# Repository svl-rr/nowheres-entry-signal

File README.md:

# SVL (Nowheres) Yard Entry Signal Driver

This is Arduino firmware for a microcontroller that has a pushbutton that
the yardmaster pushes to clear the signal. When the button is pressed,
the signal goes green for a constant amount of time and the buzzer plays
a chirping tone. After the time is up, the signal goes red again.

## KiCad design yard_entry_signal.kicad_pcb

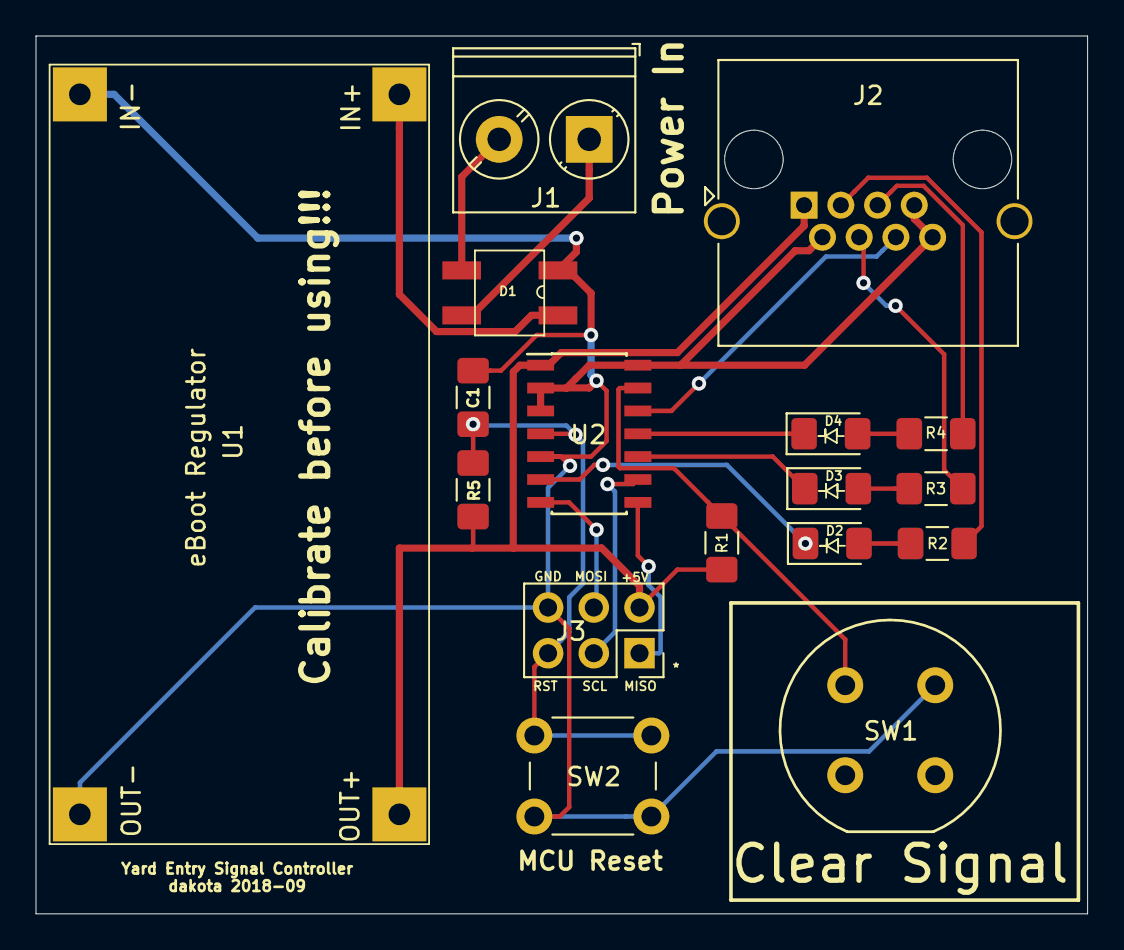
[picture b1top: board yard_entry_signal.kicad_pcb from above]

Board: 2 copper layers, 58.4 x 48.8 mm, 17 parts (0 on the bottom side), 20 nets.

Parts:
C1: 10uF; C_1206_3216Metric_Pad1.42x1.75mm_HandSolder
D1: Rect; MBS
D2: Red; LED_1206_HandSolder_Marked
D3: Yellow; LED_1206_HandSolder_Marked
D4: Green; LED_1206_HandSolder_Marked
J1: Conn_01x02; TerminalBlock_Phoenix_PT-1,5-2-5.0-H_1x02_P5.00mm_Horizontal
J2: RJ45; RJ45_Amphenol_RJHSE5380
J3: AVR-ISP-6; PinSocket_2x03_P2.54mm_Vertical
R1, R5: 10k; R_1206_3216Metric_Pad1.42x1.75mm_HandSolder
R2, R3, R4: 390; R_1206_3216Metric_Pad1.42x1.75mm_HandSolder
SW1: UsrBtn; Push_E-Switch_KS01Q01
SW2: Reset; SW_PUSH_6mm_H5mm
U1: eboot_regulator
U2: ATtiny44A-SSU; SOIC-14_3.9x8.7mm_P1.27mm

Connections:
+5V: J2.1, J3.2, R1.1, R5.2, U1.3, U2.1
/AC_PWR_1: D1.4, J1.2
/AC_PWR_2: D1.3, J1.1
/ATTiny44A/PA0: R1.2, SW1.1, U2.13
/ATTiny44A/PA2: D4.1, U2.11
/ATTiny44A/PA3: D3.1, U2.10
/ATTiny44A/PA7: D2.1, U2.6
/ATTiny44A/RESET_PB3: C1.1, J3.5, R5.1, SW2.1, U2.4
/ATTiny44A/SPI_MISO_PA5: J3.1, U2.8
/ATTiny44A/SPI_MOSI_PA6: J3.4, U2.7
/ATTiny44A/SPI_SCL_PA4: J3.3, U2.9
/Yard Signal Jack/Buzzer: J2.6, U2.12
/Yard Signal Jack/Green_Drain: J2.5, R4.2
/Yard Signal Jack/Red_Drain: J2.3, R2.2
/Yard Signal Jack/Yellow_Drain: J2.4, R3.2
GND: C1.2, D1.2, J2.2, J2.7, J2.8, J3.6, SW1.2, SW2.2, U1.2, U1.4, U2.2, U2.3, U2.5, U2.14
unnamed: D1.1, U1.1
unnamed: D2.2, R2.1
unnamed: D3.2, R3.1
unnamed: D4.2, R4.1

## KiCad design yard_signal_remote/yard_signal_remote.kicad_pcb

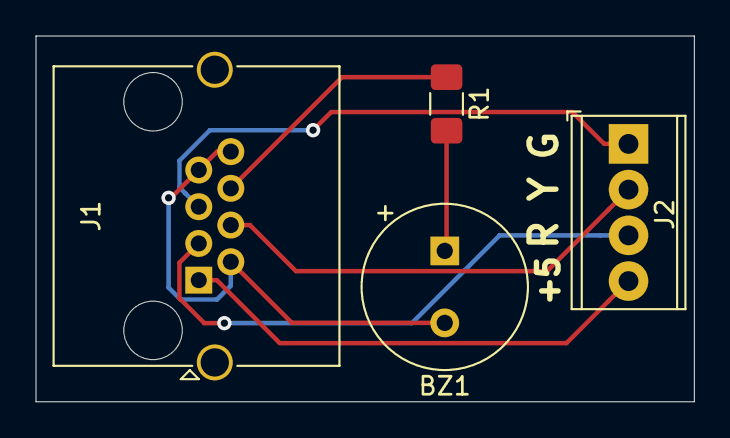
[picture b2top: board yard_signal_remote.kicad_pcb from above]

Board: 2 copper layers, 36.6 x 20.3 mm, 4 parts (0 on the bottom side), 7 nets.

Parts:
BZ1: Buzzer; MagneticBuzzer_CUI_CST-931RP-A
J1: RJ45; RJ45_Amphenol_RJHSE5380
J2: Conn_01x04_Female; TerminalBlock_Phoenix_MPT-0,5-4-2.54_1x04_P2.54mm_Horizontal
R1: 100; R_1206_3216Metric_Pad1.42x1.75mm_HandSolder

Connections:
+5V: J1.1, J2.4
/Buzzer: J1.6, R1.1
/Green_Drain: J1.5, J2.1
/Red_Drain: J1.3, J2.3
/Yellow_Drain: J1.4, J2.2
GND: BZ1.2, J1.2, J1.7, J1.8
unnamed: BZ1.1, R1.2

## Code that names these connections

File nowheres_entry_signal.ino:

#define SIGNAL_RED_PIN 7  // PA7, Tiny 6
#define SIGNAL_YELLOW_PIN 3  // PA3, Tiny 10
#define SIGNAL_GREEN_PIN 2  // PA2, Tiny 11
#define BUZZER_PIN 1  // Tiny 12
#define BUTTON_PIN 0 // PA0, Tiny 13
// #define LED_L_PIN 13

#define GREEN_TIME_MS 25000
#define YELLOW_TIME_MS 0  // disabled for now

#define BUZZER_NOTE_LENGTH_MS 20
#define BUZZER_REST_LENGTH_MS 50
#define BUZZER_TOTAL_SONG_LENGTH_MS 2000
#define BUZZER_PERIOD_MS (BUZZER_NOTE_LENGTH_MS + BUZZER_REST_LENGTH_MS)

unsigned long buttonPressedMs = 0;
unsigned short buzzerNoteAndRestStartTimeMs = 0;

void SetSignal(const int onPin) {
  digitalWrite(SIGNAL_RED_PIN, HIGH);
  digitalWrite(SIGNAL_YELLOW_PIN, HIGH);
  digitalWrite(SIGNAL_GREEN_PIN, HIGH);
  digitalWrite(onPin, LOW);
}

void PokeBuzzer(const unsigned long now_ms) {
  unsigned long msSinceButtonPress = now_ms - buttonPressedMs;
  if (buttonPressedMs > 0 && msSinceButtonPress < BUZZER_TOTAL_SONG_LENGTH_MS) {
    if (buzzerNoteAndRestStartTimeMs == 0) {
      buzzerNoteAndRestStartTimeMs = now_ms;
    }

    unsigned long currentNoteDurationMs = now_ms - buzzerNoteAndRestStartTimeMs;
    if (currentNoteDurationMs < BUZZER_NOTE_LENGTH_MS) {
      digitalWrite(BUZZER_PIN, HIGH);
    } else if (currentNoteDurationMs < BUZZER_PERIOD_MS) {
      digitalWrite(BUZZER_PIN, LOW);
    } else {
      // start a new note
      buzzerNoteAndRestStartTimeMs = 0;
    }
  } else {
    buzzerNoteAndRestStartTimeMs = 0;
    digitalWrite(BUZZER_PIN, LOW);
  }
}

void setup() {
  pinMode(SIGNAL_RED_PIN, OUTPUT);
  pinMode(SIGNAL_YELLOW_PIN, OUTPUT);
  pinMode(SIGNAL_GREEN_PIN, OUTPUT);
  pinMode(BUZZER_PIN, OUTPUT);
  pinMode(BUTTON_PIN, INPUT_PULLUP);
  // pinMode(LED_L_PIN, OUTPUT);

  SetSignal(SIGNAL_RED_PIN);
}

void loop() {
  unsigned long now_ms = millis();
  if (digitalRead(BUTTON_PIN) == LOW) { // active
    buttonPressedMs = now_ms;
    // digitalWrite(LED_L_PIN, HIGH);
    SetSignal(SIGNAL_GREEN_PIN);
  } else {
    // digitalWrite(LED_L_PIN, LOW);
  }

  PokeBuzzer(now_ms);

  unsigned long msSinceButtonPress = now_ms - buttonPressedMs;
  if (msSinceButtonPress > (GREEN_TIME_MS + YELLOW_TIME_MS)) {
    SetSignal(SIGNAL_RED_PIN);
  } else if (msSinceButtonPress > GREEN_TIME_MS) {
    SetSignal(SIGNAL_YELLOW_PIN);
  }
}

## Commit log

2018-06-24 Initial commit for rev 0 of nowheres yard entry signal driver
2018-06-24 Add readme
2018-11-30 Change pins to match ATTiny44A.
2018-11-30 Add PCBs for yard signal project
